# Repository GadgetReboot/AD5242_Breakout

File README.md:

# AD5242_Breakout
<br><br><BR><BR>
AD5242 Digital Potentiometer Breakout Board

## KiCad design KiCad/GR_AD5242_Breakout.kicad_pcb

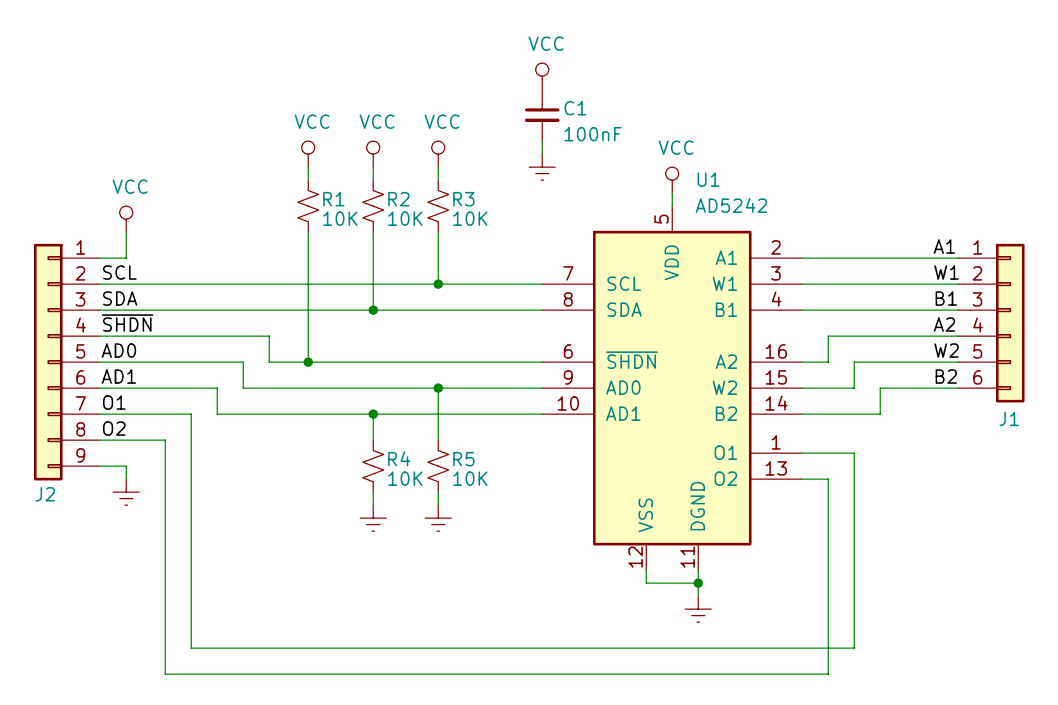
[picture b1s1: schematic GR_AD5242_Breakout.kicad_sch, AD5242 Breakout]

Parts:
C1: 100nF; C_0805_2012Metric_Pad1.15x1.40mm_HandSolder
J1: Conn_01x06; PinHeader_1x06_P2.54mm_Vertical
J2: Conn_01x09; PinHeader_1x09_P2.54mm_Vertical
R1, R2, R3, R4, R5: 10K; R_0805_2012Metric_Pad1.20x1.40mm_HandSolder
U1: AD5242; TSSOP-16_4.4x5mm_P0.65mm

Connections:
/A1: J1.1, U1.2 (A1)
/A2: J1.4, U1.16 (A2)
/AD0: J2.5, R5.1, U1.9 (AD0)
/AD1: J2.6, R4.1, U1.10 (AD1)
/B1: J1.3, U1.4 (B1)
/B2: J1.6, U1.14 (B2)
/O1: J2.7, U1.1 (O1)
/O2: J2.8, U1.13 (O2)
/SCL: J2.2, R3.2, U1.7 (SCL)
/SDA: J2.3, R2.2, U1.8 (SDA)
/W1: J1.2, U1.3 (W1)
/W2: J1.5, U1.15 (W2)
/~SHDN: J2.4, R1.2, U1.6 (~SHDN)
GNDREF: C1.2, J2.9, R4.2, R5.2, U1.11 (DGND), U1.12 (VSS)
VCC: C1.1, J2.1, R1.1, R2.1, R3.1, U1.5 (VDD)

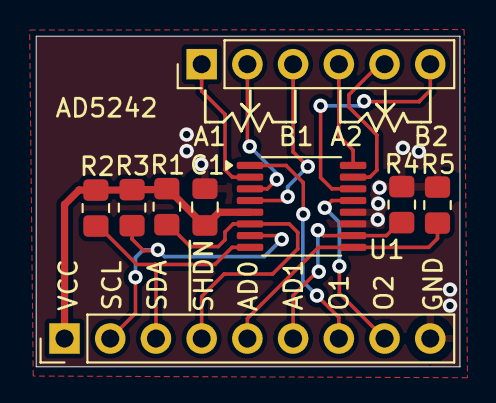
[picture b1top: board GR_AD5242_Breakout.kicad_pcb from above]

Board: 2 copper layers, 23.5 x 18.4 mm, 9 parts (0 on the bottom side), 15 nets.
